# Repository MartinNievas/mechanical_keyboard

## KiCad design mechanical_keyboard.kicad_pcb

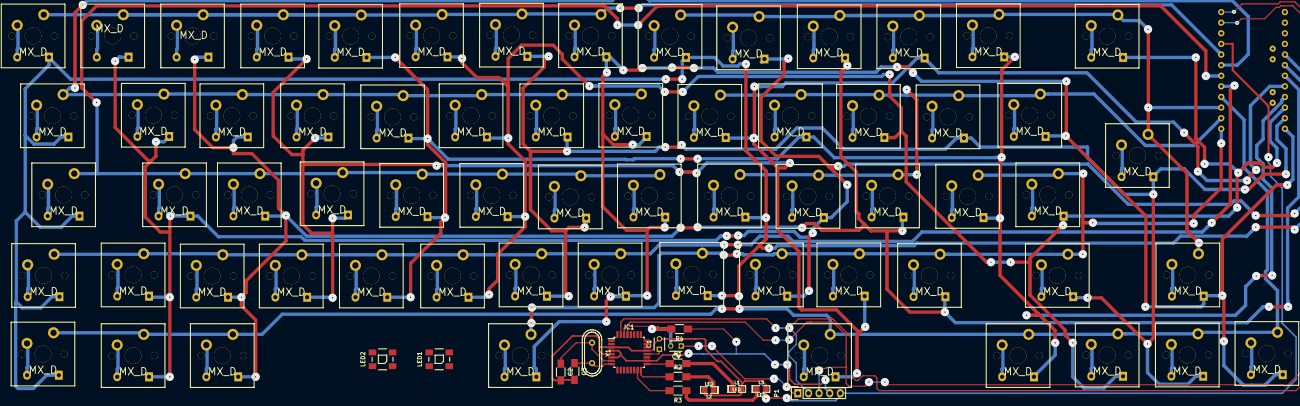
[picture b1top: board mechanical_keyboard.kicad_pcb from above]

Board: 2 copper layers, 81 parts (0 on the bottom side), 97 nets.

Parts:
C1: 0.1uF; C_Disc_D3_P2.5
C2, C3: 22pF; C_1206_HandSoldering
C4: 100nF; C_Disc_D3_P2.5
IC1: ATMEGA328P-A; TQFP-32_7x7mm_Pitch0.8mm
L1, L2, L3: LED; LED_0805
LED1, LED2: WS2812B
P1: CONN_01X05; Pin_Header_Straight_1x05
R1, R2: R; R_1206_HandSoldering
R3: 330; R_1206_HandSoldering
R4: 10k; R_1206_HandSoldering
SW1, SW2, SW3, SW4, SW5, SW6, SW7, SW8, SW9, SW10, SW11, SW12, SW13, SW14, SW15, SW16, SW17, SW18, SW19, SW20, SW21, SW22, SW23, SW24, SW25, SW26, SW27, SW28, SW29, SW30, SW31, SW32, SW33, SW34, SW35, SW36, SW37, SW38, SW39, SW40, SW41, SW42, SW43, SW44, SW45, SW46, SW47, SW48, SW49, SW50, SW51, SW52, SW53, SW54, SW55, SW56, SW57, SW58, SW59, SW60, SW61, SW62, SW63, SW64: MX_D; SW_PCB_4PIN
Y1: Crystal; Crystal_HC49-U_Vertical
uP1: ARDUPROMINI-6; ArduProMini-6

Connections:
/LED_controller/DTR: C4.1, P1.1
/LED_controller/Din: IC1.32, LED1.4
/LED_controller/LED_0: IC1.17, R1.1
/LED_controller/LED_1: IC1.16, R2.1
/LED_controller/LED_2: IC1.15, R3.2
/LED_controller/LED_RX: IC1.30, P1.3, uP1.8
/LED_controller/LED_TX: IC1.31, P1.2, uP1.7
/LED_controller/xtal1: C2.1, IC1.7, Y1.1
/LED_controller/xtal2: C3.1, IC1.8, Y1.2
/keyboard_matrix/col0: SW1.4, SW2.4, SW3.4, SW4.4, SW5.4, SW6.4, SW7.4, SW8.4, uP1.23
/keyboard_matrix/col1: SW9.4, SW10.4, SW11.4, SW12.4, SW13.4, SW14.4, SW15.4, SW16.4, uP1.24
/keyboard_matrix/col2: SW17.4, SW18.4, SW19.4, SW20.4, SW21.4, SW22.4, SW23.4, SW24.4, uP1.25
/keyboard_matrix/col3: SW25.4, SW26.4, SW27.4, SW28.4, SW29.4, SW30.4, SW31.4, SW32.4, uP1.26
/keyboard_matrix/col4: SW33.4, SW34.4, SW35.4, SW36.4, SW37.4, SW38.4, SW39.4, SW40.4, uP1.27
/keyboard_matrix/col5: SW41.4, SW42.4, SW43.4, SW44.4, SW45.4, SW46.4, SW47.4, SW48.4, uP1.28
/keyboard_matrix/col6: SW49.4, SW50.4, SW51.4, SW52.4, SW53.4, SW54.4, SW55.4, SW56.4, uP1.29
/keyboard_matrix/col7: SW57.4, SW58.4, SW59.4, SW60.4, SW61.4, SW62.4, SW63.4, SW64.4, uP1.30
/keyboard_matrix/row0: SW1.1, SW9.1, SW17.1, SW25.1, SW33.1, SW41.1, SW49.1, SW57.1, uP1.11
/keyboard_matrix/row1: SW2.1, SW10.1, SW18.1, SW26.1, SW34.1, SW42.1, SW50.1, SW58.1, uP1.12
/keyboard_matrix/row2: SW3.1, SW11.1, SW19.1, SW27.1, SW35.1, SW43.1, SW51.1, SW59.1, uP1.13
/keyboard_matrix/row3: SW4.1, SW12.1, SW20.1, SW28.1, SW36.1, SW44.1, SW52.1, SW60.1, uP1.14
/keyboard_matrix/row4: SW5.1, SW13.1, SW21.1, SW29.1, SW37.1, SW45.1, SW53.1, SW61.1, uP1.15
/keyboard_matrix/row5: SW6.1, SW14.1, SW22.1, SW30.1, SW38.1, SW46.1, SW54.1, SW62.1, uP1.16
/keyboard_matrix/row6: SW7.1, SW15.1, SW23.1, SW31.1, SW39.1, SW47.1, SW55.1, SW63.1, uP1.17
/keyboard_matrix/row7: SW8.1, SW16.1, SW24.1, SW32.1, SW40.1, SW48.1, SW56.1, SW64.1, uP1.18
GND: C1.2, C2.2, C3.2, IC1.3, IC1.5, IC1.21, L1.2, L2.2, L3.2, LED1.3, LED2.3, P1.5, uP1.10
unnamed: C1.1, IC1.20
unnamed: C4.2, IC1.29, R4.2
unnamed: L1.1, R1.2
unnamed: L2.1, R2.2
unnamed: L3.1, R3.1
unnamed: LED1.2, LED2.4
unnamed: SW1.2, SW1.3
unnamed: SW2.2, SW2.3
unnamed: SW3.2, SW3.3
unnamed: SW4.2, SW4.3
unnamed: SW5.2, SW5.3
unnamed: SW6.2, SW6.3
unnamed: SW7.2, SW7.3
unnamed: SW8.2, SW8.3
unnamed: SW9.2, SW9.3
unnamed: SW10.2, SW10.3
unnamed: SW11.2, SW11.3
unnamed: SW12.2, SW12.3
unnamed: SW13.2, SW13.3
unnamed: SW14.2, SW14.3
unnamed: SW15.2, SW15.3
unnamed: SW16.2, SW16.3
unnamed: SW17.2, SW17.3
unnamed: SW18.2, SW18.3
unnamed: SW19.2, SW19.3
unnamed: SW20.2, SW20.3
unnamed: SW21.2, SW21.3
unnamed: SW22.2, SW22.3
unnamed: SW23.2, SW23.3
unnamed: SW24.2, SW24.3
unnamed: SW25.2, SW25.3
unnamed: SW26.2, SW26.3
unnamed: SW27.2, SW27.3
unnamed: SW28.2, SW28.3
unnamed: SW29.2, SW29.3
unnamed: SW30.2, SW30.3
unnamed: SW31.2, SW31.3
unnamed: SW32.2, SW32.3
unnamed: SW33.2, SW33.3
unnamed: SW34.2, SW34.3
unnamed: SW35.2, SW35.3
unnamed: SW36.2, SW36.3
unnamed: SW37.2, SW37.3
unnamed: SW38.2, SW38.3
unnamed: SW39.2, SW39.3
unnamed: SW40.2, SW40.3
unnamed: SW41.2, SW41.3
unnamed: SW42.2, SW42.3
unnamed: SW43.2, SW43.3
unnamed: SW44.2, SW44.3
unnamed: SW45.2, SW45.3
unnamed: SW46.2, SW46.3
unnamed: SW47.2, SW47.3
unnamed: SW48.2, SW48.3
unnamed: SW49.2, SW49.3
unnamed: SW50.2, SW50.3
unnamed: SW51.2, SW51.3
unnamed: SW52.2, SW52.3
unnamed: SW53.2, SW53.3
unnamed: SW54.2, SW54.3
unnamed: SW55.2, SW55.3
unnamed: SW56.2, SW56.3
unnamed: SW57.2, SW57.3
unnamed: SW58.2, SW58.3
unnamed: SW59.2, SW59.3
unnamed: SW60.2, SW60.3
unnamed: SW61.2, SW61.3
unnamed: SW62.2, SW62.3
unnamed: SW63.2, SW63.3
unnamed: SW64.2, SW64.3
VCC: IC1.4, IC1.6, IC1.18, LED1.1, LED2.1, P1.4, R4.1
